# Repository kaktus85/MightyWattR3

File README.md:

# MightyWatt R3
Resources for MightyWatt R3 electronic load.
This repository contains all the available documentation and source files for MightyWatt R3 electronic load project.
- a copy of this is also available on Google Drive: https://drive.google.com/drive/folders/0B7G3xJXZNLUpWmUxd0lfckF5STg?resourcekey=0-LSW1TeSUeF5TF7GDGjf21w&usp=sharing
- an easy to read description of the various folders is here: http://kaktuscircuits.blogspot.cz/2017/03/mightywatt-r3-resource-page.html
- MightyWatt R3 can be purchased through Tindie: https://www.tindie.com/products/Kaktus/mightywatt-70w-electronic-load-for-arduino/

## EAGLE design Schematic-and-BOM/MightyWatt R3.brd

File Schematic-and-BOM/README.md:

# Schematic, board and BOM
- Eagle source files for the PCB of MightyWatt R3.
- A PDF schematic also included for a quick reference without having to install Eagle.
- PDF Bill of Materials.

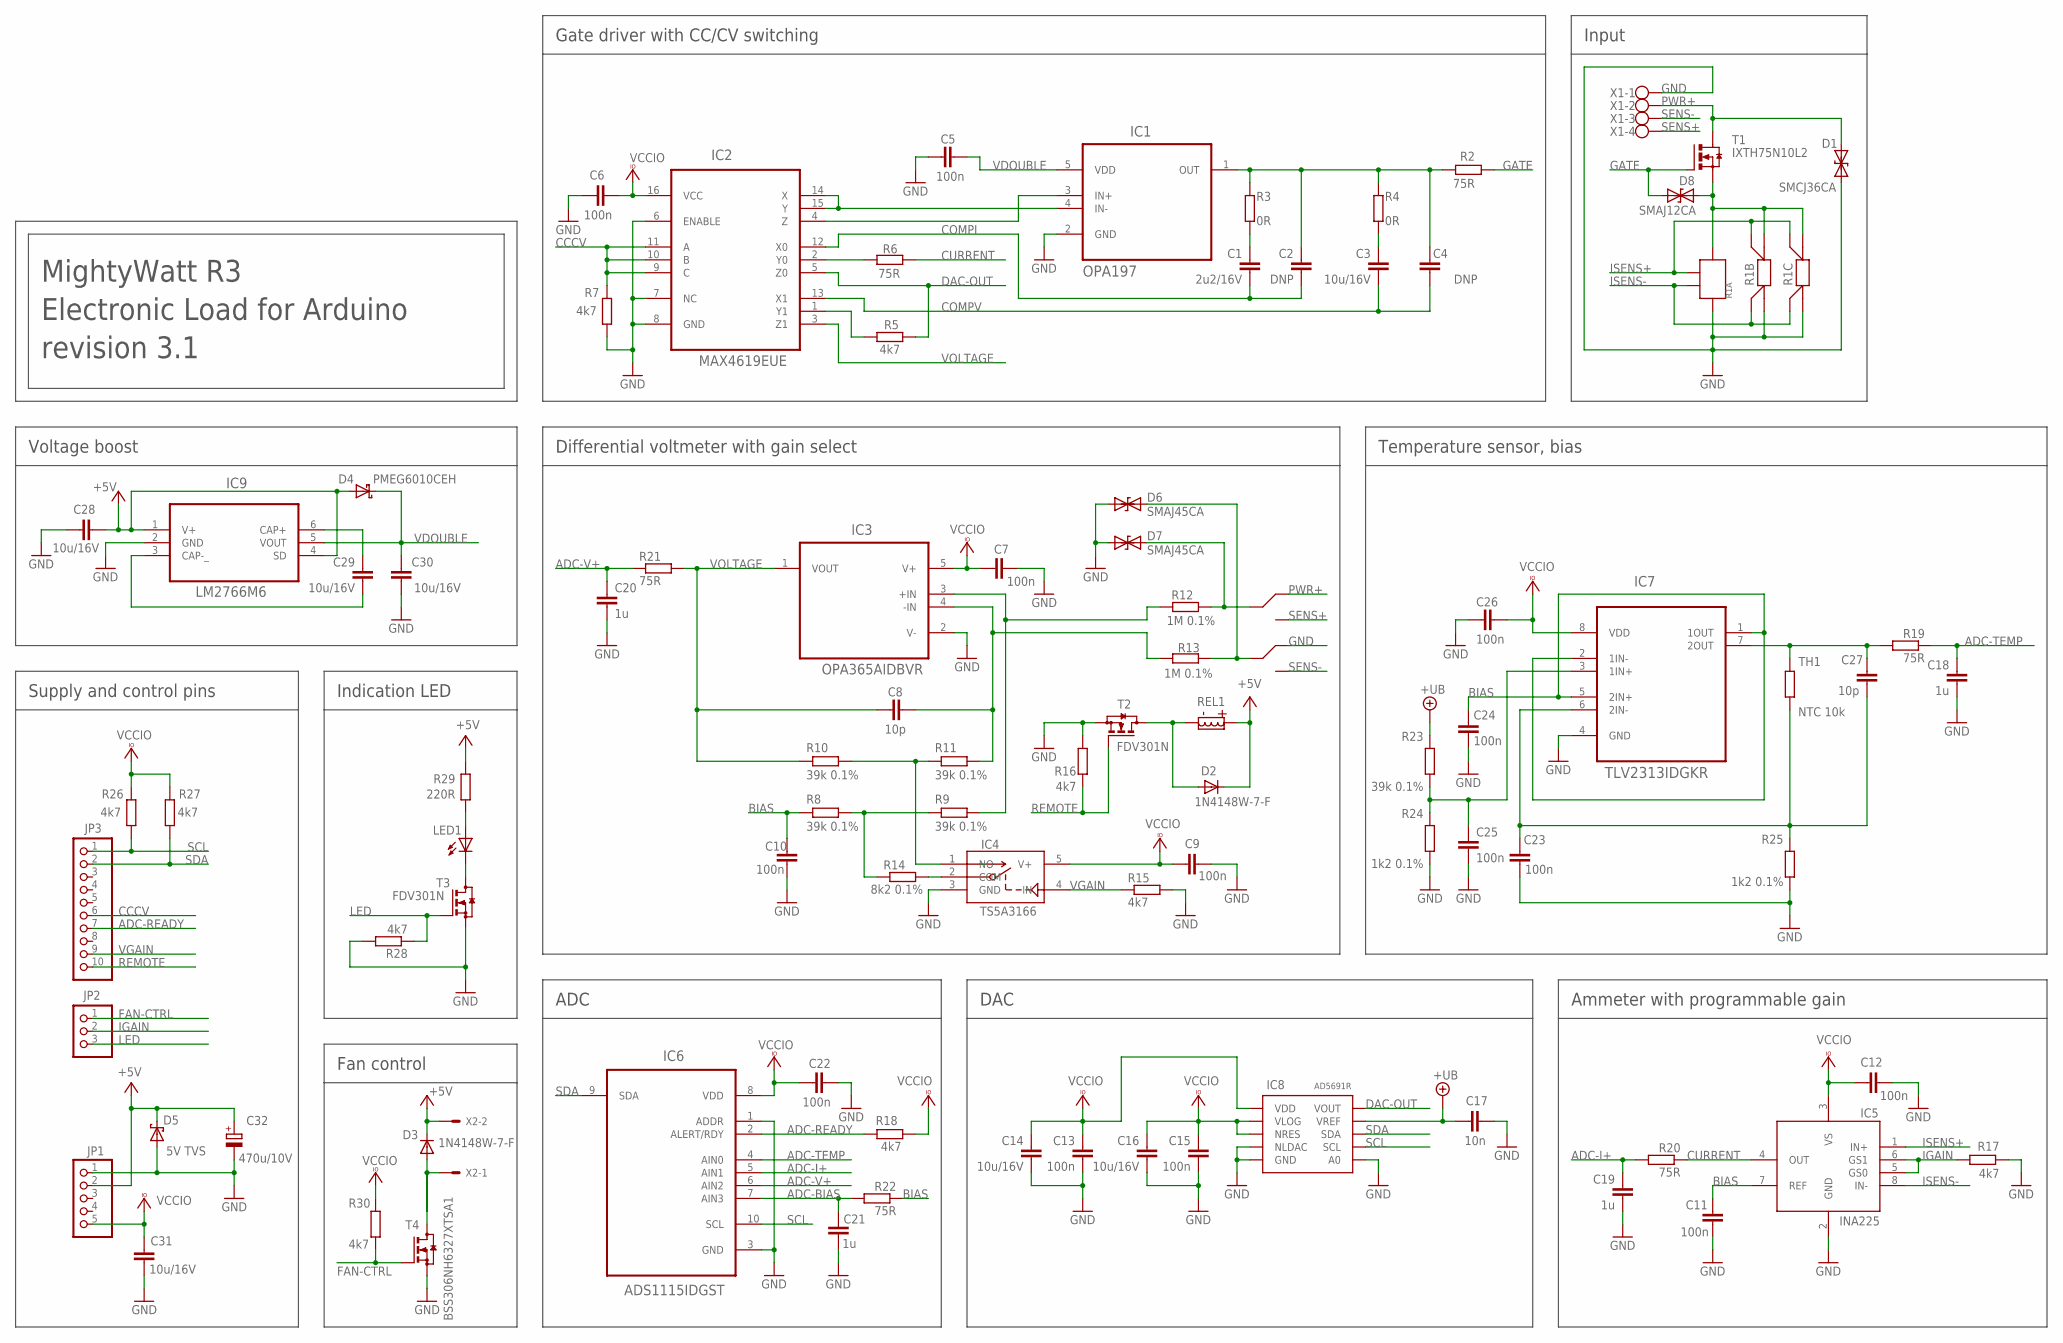
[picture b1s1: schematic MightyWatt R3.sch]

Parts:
C1: 2u2/16V; C1206
C2, C4: DNP; C0603
C3, C14, C16, C28, C29, C30, C31: 10u/16V; C1206
C5, C6, C7, C9, C10, C11, C12, C13, C15, C22, C23, C24, C25, C26: 100n; C0603
C8, C27: 10p; C0603
C17: 10n; C0603
C18, C19, C20, C21: 1u; C0603
C32: 470u/10V; SMC_E; PARTN TPSB476K010R0250
D1: SMCJ36CA; SMC
D2, D3: 1N4148W-7-F; SOD123
D4: PMEG6010CEH; SOD123
D5: 5V TVS; SMB
D6, D7: SMAJ45CA; DO-214AC
D8: SMAJ12CA; DO-214AC
IC1: TLV271IDBVR; SOT95P280X145-5N; MPN OPA197
IC2: MAX4619EUE; SOP65P640X120-16N
IC3: OPA365AIDBVR; SOT95P280X145-5N
IC4: TS5A3166; SC70-5
IC5: INA225; MSOP8
IC6: ADS1115IDGST; SOP50P490X110-10N; MPN ADS1015IDGST
IC7: TLV2372IDGK; SOP65P490X110-8N; MPN TLV2313IDGKR
IC8: AD5691RAD5691R; SOP50P490X110-10N
IC9: LM2766M6; SOT95P285X122-6N
JP1: SUPPLY; 1X05
JP2: CONTROL, LED; 1X03
JP3: TWI; 1X10
LED1: LEDCHIP-LED0805; CHIP-LED0805
R1A: WSL3637; POWER-R-4TERM
R1B: LVK24
R1C: LVK12; 1206-4WIRE
R2, R6, R19, R20, R21, R22: 75R; R0603
R3, R4: 0R; R0603
R5, R7, R15, R16, R17, R18, R26, R27, R28, R30: 4k7; R0603
R8, R9, R10, R11, R23: 39k 0.1%; R0603
R12, R13: 1M 0.1%; R0603
R14: 8k2 0.1%; R0603
R24, R25: 1k2 0.1%; R0603
R29: 220R; R0603
REL1: IM03NS; IM03NS-NARROW-RELAY
T1: IXTH75N10L2; TO247-BLANK
T2, T3: BSS123; SOT23; PARTNAME FDV301N
T4: BSS123; SOT23; PARTNAME BSS306NH6327XTSA1
TH1: NTC 10k; R0402
X1: W237-4
X2: 22-23-2021

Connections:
+5V: C28.1, C32.+, D2.C, D3.C, D4.A, D5.C, IC9.1 (V+), IC9.4 (SD), JP1.2, R29.1, REL1.P$1 (C+), X2.2
+UB: C17.2, IC8.9 (VREF), R23.2
ADC-BIAS: C21.2, IC6.7 (AIN3), R22.2
ADC-I+: C19.2, IC6.5 (AIN1), R20.2
ADC-READY: IC6.2 (ALERT/RDY), JP3.7, R18.1
ADC-TEMP: C18.2, IC6.4 (AIN0), R19.1
ADC-V+: C20.2, IC6.6 (AIN2), R21.1
BIAS: C10.2, C11.2, C24.2, IC5.7 (REF), IC7.1 (1OUT), IC7.2 (1IN-), IC7.5 (2IN+), R8.1, R22.1
CCCV: IC2.9 (C), IC2.10 (B), IC2.11 (A), JP3.6, R7.2
COMPI: C1.1, C2.1, IC2.12 (X0)
COMPV: C3.1, C4.1, IC2.13 (X1)
CURRENT: IC5.4 (OUT), R6.1, R20.1
DAC-OUT: IC2.5 (Z0), IC8.10 (VOUT), R5.1
FAN-CTRL: JP2.1, R30.2, T4.1 (G)
GATE: D8.C, R2.1, T1.G
GND: C5.1, C6.2, C7.2, C9.1, C10.1, C11.1, C12.2, C13.1, C14.2, C15.1, C16.2, C17.1, C18.1, C19.1, C20.1, C21.1, C22.2, C23.1, C24.1, C25.1, C26.2, C28.2, C30.2, C31.2, C32.-, D1.A, D5.A, D6.A, D7.A, IC1.2 (GND), IC2.6 (ENABLE), IC2.7 (NC), IC2.8 (GND), IC3.2 (V-), IC4.3 (GND), IC5.2 (GND), IC6.1 (ADDR), IC6.3 (GND), IC7.4 (GND), IC8.4 (NLDAC), IC8.5 (GND), IC8.6 (A0), IC9.2 (GND), JP1.1, R1A.POWER1, R1B.I1, R1C.I1, R7.1, R15.2, R16.1, R17.1, R24.1, R25.1, R28.2, REL1.P$2 (NC), T2.2 (S), T3.2 (S), T4.2 (S), X1.1
IGAIN: IC5.5 (GS0), IC5.6 (GS1), JP2.2, R17.2
ISENS+: IC5.1 (IN+), R1A.SENSE2, R1B.V2, R1C.V2
ISENS-: IC5.8 (IN-), R1A.SENSE1, R1B.V1, R1C.V1
LED: JP2.3, R28.1, T3.1 (G)
unnamed: IC1.3 (IN+), IC2.4 (Z)
unnamed: IC2.2 (Y0), R6.2
unnamed: C23.2, C27.1, IC7.6 (2IN-), R25.2, TH1.1
unnamed: LED1.C, T3.3 (D)
unnamed: C29.1, IC9.6 (CAP+)
unnamed: C29.2, IC9.3 (CAP-_)
unnamed: C1.2, R3.2
unnamed: IC1.4 (IN-), IC2.14 (X), IC2.15 (Y)
unnamed: D8.A, R1A.POWER2, R1B.I2, R1C.I2, T1.S
unnamed: C2.2, C4.2, IC1.1 (OUT), R2.2, R3.1, R4.1
unnamed: D7.C, R12.2, REL1.P$6 (COM)
unnamed: C27.2, IC7.7 (2OUT), R19.2, TH1.2
unnamed: IC2.1 (Y1), R5.2
unnamed: LED1.A, R29.2
unnamed: D6.C, R13.1, REL1.P$3 (COM)
unnamed: C3.2, R4.2
unnamed: C25.2, IC7.3 (1IN+), R23.1, R24.2
unnamed: C8.2, IC3.4 (-IN), R11.2, R13.2
unnamed: D2.A, REL1.P$8 (C-), T2.3 (D)
unnamed: D3.A, T4.3 (D), X2.1
unnamed: IC4.1 (NO), R10.2, R11.1
unnamed: IC3.3 (+IN), R9.2, R12.1
unnamed: IC4.2 (COM), R14.2
unnamed: R8.2, R9.1, R14.1
PWR+: D1.C, REL1.P$7 (NC), T1.D, X1.2
REMOTE: JP3.10, R16.2, T2.1 (G)
SCL: IC6.10 (SCL), IC8.7 (SCL), JP3.1, R26.1
SDA: IC6.9 (SDA), IC8.8 (SDA), JP3.2, R27.1
SENS+: REL1.P$5 (NO), X1.4
SENS-: REL1.P$4 (NO), X1.3
VCCIO: C6.1, C7.1, C9.2, C12.1, C13.2, C14.1, C15.2, C16.1, C22.1, C26.1, C31.1, IC2.16 (VCC), IC3.5 (V+), IC4.5 (V+), IC5.3 (VS), IC6.8 (VDD), IC7.8 (VDD), IC8.1 (VDD), IC8.2 (VLOG), IC8.3 (NRES), JP1.5, R18.2, R26.2, R27.2, R30.1
VDOUBLE: C5.2, C30.1, D4.C, IC1.5 (VDD), IC9.5 (VOUT)
VGAIN: IC4.4 (IN), JP3.9, R15.1
VOLTAGE: C8.1, IC2.3 (Z1), IC3.1 (VOUT), R10.1, R21.2

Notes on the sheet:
Voltage boost
DAC
Temperature sensor, bias
Supply and control pins
Input
Ammeter with programmable gain
Differential voltmeter with gain select
Gate driver with CC/CV switching
MightyWatt R3 Electronic Load for Arduino revision 3.1
Indication LED
ADC
Fan control

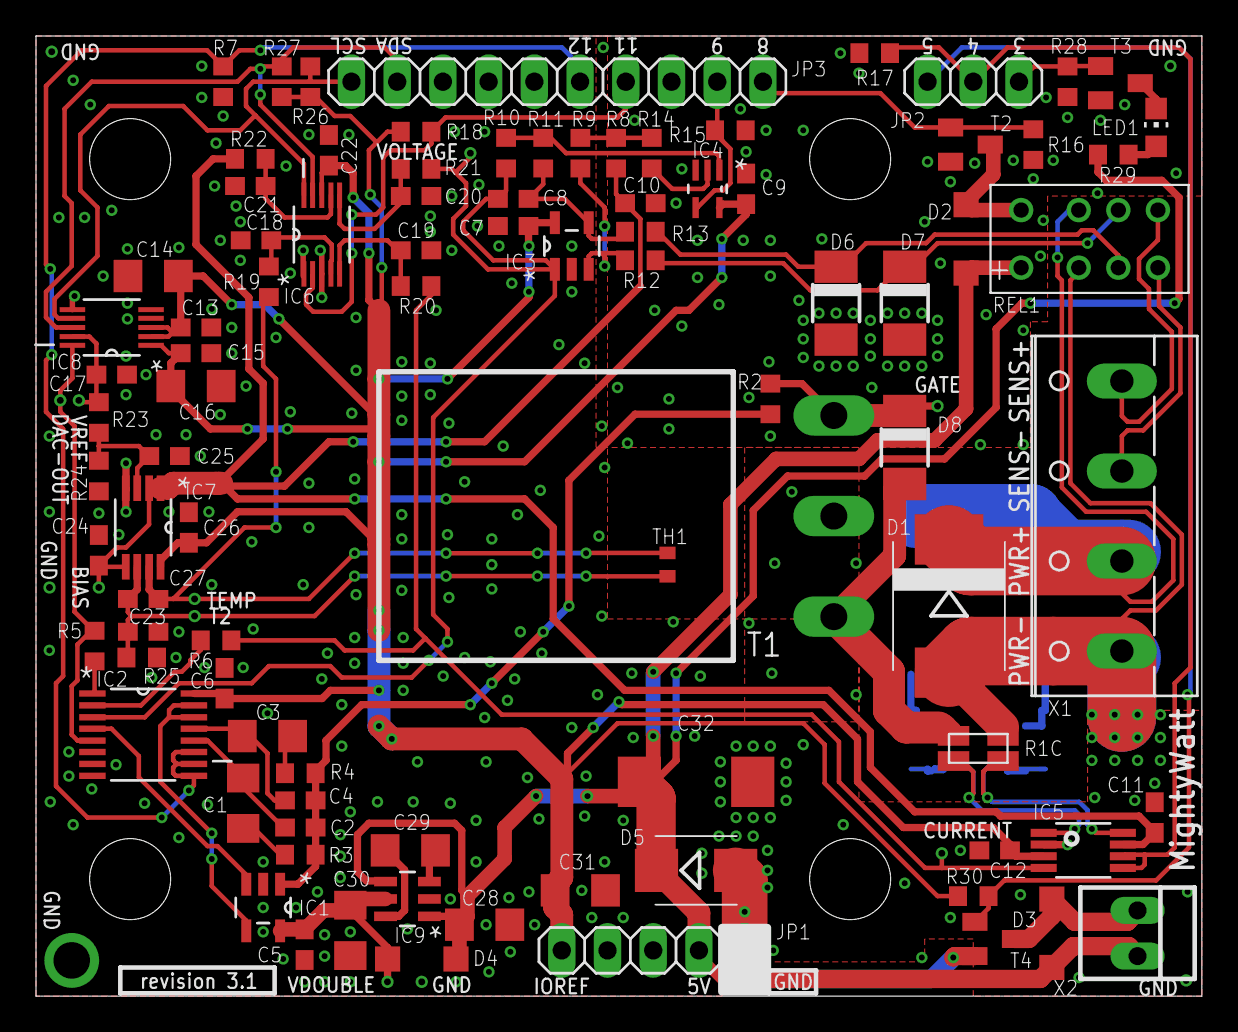
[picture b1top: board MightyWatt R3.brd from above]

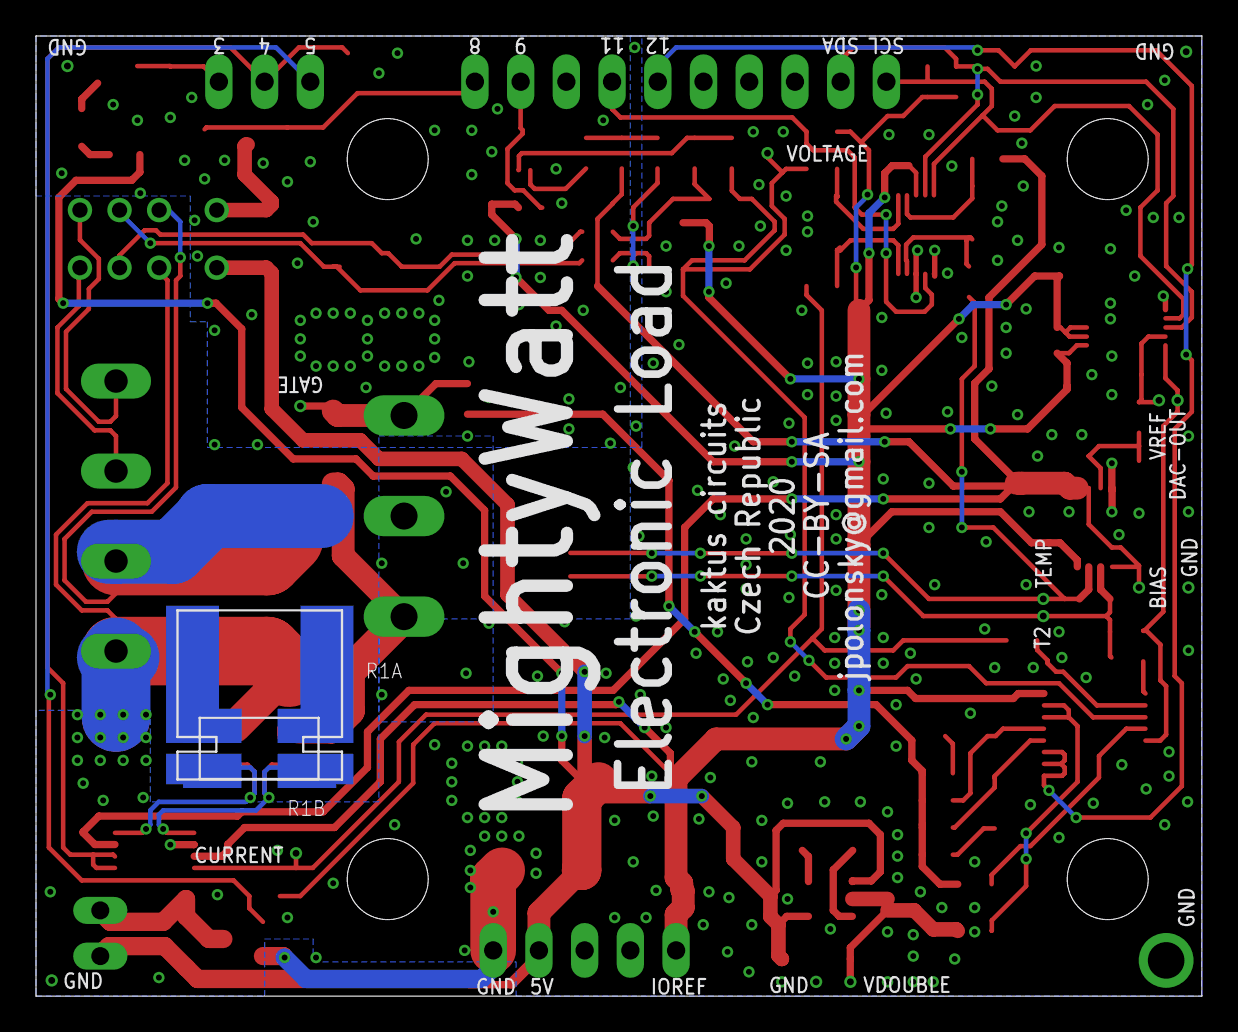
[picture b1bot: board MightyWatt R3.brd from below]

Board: 2 copper layers, 64.8 x 53.3 mm, 93 parts (3 on the bottom side), 54 nets.

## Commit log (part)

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2017-03-25 :space_invader: Added .gitattributes
2017-03-25 Uno first
2017-03-25 Schematic readme updated
2017-03-25 Updated link to resource page
2017-03-25 Update link to resource page
2017-03-25 Refactored logic of range switching
2017-03-25 Added case drawings
2017-03-26 Fixed schematic
2017-03-30 Optimized measurement loop
    Measurement loop now takes temperature measurements less frequently than
    voltage and current measurements so the report rate increased from 150
    to 220 reports per second while new temperature measurements are taken
    at least once per second, which is satisfactory.
2017-03-30 External series resistance power limit
    Added a new feature that lets user specify a power limit when using
    external series resistance. This limit then can be used to automatically
    stop the load if exceeded. Just like the regular watchdog, but for
    external series resistance.
2017-03-30 Standard configuration changed to Arduino Uno
    Arduino Uno is the recommended board in this version.
2017-03-30 Updated guides
    Added information about series resistance power watchdog
2017-03-30 Removed changelog
    Letting GitHub track the changes
2017-03-31 Fixed Arduino Zero watchdog
    Low speed clock on SAMD21 watchdog was causing synchronization delays
    that slowed down the control loop. It is now fixed and working.
2017-04-02 Schematic fix
    - Proper symbols of bi-directional TVS were added to the schematic.
    - Order of switching current and voltage ranges was upgraded to decrease
    spikes.
    - Guide was updated.
2017-04-04 Fixed a measurement glitch during range switching
    When a range is switched, it may create a transient condition (dip or
    spike). The ADC might have reported a value that had been measured over
    two different ranges. Such a value is incorrect. This is now fixed and
    measurements immediately following a range or mode (CC/CV) change are
    discarded.
2017-04-05 Fix in calibration sketch
2017-04-06 Fixed error in small number display
    - Small numbers were wrong by one order of magnitude on screen. Log was
    OK.
    - Users can now easily enter values with micro-resolution.
    - Firmware contained a possible problem with negative slopes. Fixed.
2017-04-06 Visual studio solution update
2017-04-07 Autoranging can be disabled
    Added option to disable autoranging.
    Changed/refactored the logic of saving and loading of settings and
    program items.
2017-04-07 Some constants added to flash memory
2017-04-07 Added constant resistance and power using CV
2017-04-07 Firmware version definition moved to main sketch
2017-04-07 Updated guide and communication protocol description, various bug fixes
    Bug fixes in control loop, voltage setter and current setter
2017-04-11 Initial calibration files for SN003 and SN004
2017-04-21 Calibration files SN005-SN007
2017-05-04 Added Simple ammeter mode to firmware
    Added Simple ammeter mode to firmware - sets the load to maximum current
    while keeping autoranging
2017-05-04 Simple ammeter implementation in Windows control program
2017-05-04 Changed configuration folders structure
2017-05-13 Asynchronous COM port list generation
    This commit enables asynchronous COM port list generation which means
    the GUI won't hang when you click on Connection menu. The downside is
    that it will be empty until the WMI call to Windows finishes, which can,
    in worst case, take a couple of seconds.
2017-05-27 Minor changes in detailed guide
    Typos and some clarification
2017-07-25 Calibration SN008
2017-08-06 Added calibration file for Tindie 78271
2017-08-12 Calibration files for SN010 and SN011
2017-08-14 Calibration file for SN012
2017-08-18 Calibration files for SN013 and SN014
2017-08-24 Calibration files for SN015 and SN016
2017-08-24 Folder rename to correct date
2017-08-29 Configuration file for SN017
2017-09-04 Calibration file for SN018
2017-09-12 Calibration files for SN019 and SN020
2017-09-17 Calibration files for SN021 and SN022
2017-09-23 Calibration file for SN023
2017-09-25 Updated software-controlled modes
    Proportional factor implemented to adaptive-step algorithm
2017-10-19 Calibration file for SN024
2017-10-21 Fixed incorrect fan flag in status
    Thanks to Bent for spotting this!
    In status flags, fan flag on means fan is running, as is written in the
    documentation.
2017-10-21 Increased FW revision number in FW and comm protocol description document
2017-10-24 Addes support for serial number display
    Also added support for manual pin setting for those pins that are
    uncommited on Arduino (unused by MightyWatt R3)
2017-10-27 Added support for user pins
    The new functionality lets users control unused pins on Arduino both in
    manual and program mode.
2017-10-27 Updated calibration files with serial numbers
2017-10-27 Updated user guides for 3.1.4
2017-10-27 Updated BOM with alternative (and better!) transistor IXTH80N075L2
2017-11-25 Calibration file for SN025
2017-11-28 Calibration file for SN026
2017-12-01 Calibration file for SN027
2017-12-17 Calibration file for SN028
2018-01-07 Calibration file for SN029
2018-01-10 Calibration files for SN030 and SN031
2018-01-10 Calibration file for SN032
2018-01-28 Calibration file for SN033
2018-02-04 Calibration file for SN034
2018-02-21 Calibration file for SN035
2018-03-03 Calibration file for SN036
2018-03-28 Calibration file for SN037
2018-04-03 Calibration file for SN038
2018-05-30 Calibration file for SN039
2018-06-03 Fixed a problem when the load was sometimes not reset after finishing a program and other bug fixes
    - Fixed a problem when the load was sometimes not reset after finishing a program
    - Changed timestamp format to be culture-invariant
    - Logging period should be kept more precisely now
2018-06-03 Changed behaviour for automatic file saving to save each second
    This should fix the situation where host computer has slow file writing. Previously, each log line was saved immediately, which could result in more than 100 writes per second, slowing down the progr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
2018-06-08 Bug fixes
    Culture-invariant time format in logs
    Better exception handling in communication loop
    Larger serial port buffer
2018-06-25 Calibration file for SN040
2018-07-02 Calibration file for SN041
2018-10-16 Added calibration file for SN043
2018-10-23 Calibration file for SN044
2018-11-23 Calibration file for SN045
2018-11-27 Added calibration file for SN046
2018-12-01 Fixed rounding for low current and voltage ranges
2018-12-01 Calibration file for SN047
2018-12-01 Increased FW version
2018-12-25 Calibration file for SN048
2018-12-26 Watchdog and skip modes now support temperature
    Also fixed issues where some units were not displayed correctly
    Changed system timestamp format to hh:mm:ss.sss or hh:mm:ss,sss, depending on local culture settings
2019-01-03 Calibration file for SN049
2019-01-18 Calibration files for SN050 and SN051
2019-01-18 Watchdog textbox will show incorrectly formatted values
2019-01-20 Power will not be limit-checked in application but only in hardware to allow short-term overload
2019-02-02 Gitignore change
2019-02-19 Changed silkscreen on board for easier pin identification
2019-02-19 Calibration file for SN052 to SN055
2019-02-20 Calibration files for SN056 to SN058
2019-03-06 Calibration file for SN059
2019-04-08 Calibration files for SN060 to SN066
2019-04-08 Added calibration file for SN067
2019-04-22 Calibration files for SN068 and SN069
2019-05-05 Calibration file for SN070
2019-05-13 Calibration file for SN071
2019-05-18 Calibration file for SN072
2019-06-21 Calibration files for SN073 to SN078
2019-07-14 Calibration files for SN079-SN082
2019-08-09 Added calibration file for SN083
2019-08-28 Calibration file for SN084
2019-09-07 Calibration files for SN085 to SN088
2019-11-01 Calibration file for SN089
2019-11-20 Calibration file for SN090
2019-12-13 Calibration file for SN091
2020-01-21 Calibration file for SN092
2020-01-28 Calibration file for SN093
2020-02-12 Calibration files for SN094 to SN098
2020-03-17 Rearranged wires to prevent solder bridges
2020-03-17 Calibration files for SN099 to SN102
2020-06-04 Calibration files for SN103 to SN107
2020-06-21 Fix for incorrect folder name in SN103 to SN107
2020-06-21 Calibration files for SN108 and SN109
2020-06-24 Calibration file for SN110
2020-08-25 Calibration files for SN111 to SN115
2020-08-31 Calibration files for SN116 and SN117
2020-11-18 Calibration file for SN118 and SN119
2020-11-18 Folder name fix
2020-12-01 MPPT constant program item is set only at the beginning of program step
2020-12-02 Edit gitignore, except release exe build
2020-12-02 Stop tracking some visual studio user files
2020-12-05 Snapshots in integrators and statistics are saved immediately instead of former deferred saving
2020-12-05 Fixed a bug where wrong filtered values were produced immediately after range switching
    Filter queue now automatically resets when range is switched. Until the queue is refilled with samples, the latest sample (~unfiltered value) is used.
2020-12-12 Fixed issue where program would crash in certain operations with log file
    Fixed issue where voltage and current values could have mixed filter status (one filtered, the other unfiltered)
2021-09-27 Calibration files for SN120 to SN122
2021-09-28 Added default GNUplot path for 64-bit GNUplot
2021-10-05 Calibration file for SN123
2021-10-15 Calibration files for SN124 to SN126
2021-11-05 Calibration file for SN127
2022-01-14 Calibration file for SN128
2022-01-16 Calibration file for SN129
2022-02-04 Calibration file for SN130
2022-02-12 Calibration files for SN131 and SN132
2022-05-16 Periodic flush of data to disk
    Log data are flushed every second to prevent data loss
2022-05-27 Calibration files for SN133 to SN138
2022-06-07 Calibration files for SN139 to SN163
2022-06-24 Calibration files for SN164 to SN169
2022-09-07 Calibration files for SN170 to SN175
2022-11-13 Calibration files for SN176 to SN180
2023-03-01 Calibration file for SN181
2023-03-31 Folder rename
2023-04-30 Calibration file for SN182
2023-08-28 Calibration files for SN183 and SN184
2023-09-08 Calibration file for SN186 and SN187
2025-05-22 Calibration files for SN188 to SN211
2025-09-26 Calibration files for SN212 to SN221

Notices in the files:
Schematic-and-BOM/MightyWatt R3.brd:
CC-BY-SA
